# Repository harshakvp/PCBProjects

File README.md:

# PCB Design Projects

A collection of PCB design projects developed as part of my learning journey in electronics, embedded systems, and hardware design. This repository contains projects created using industry-standard EDA tools such as **Altium Designer** and **KiCad**, along with design files, documentation, and manufacturing outputs.

---

## Projects

### 1. ESP32 With USB-C (Altium Designer)

A custom 4-layer ESP32-S3 development board featuring USB Type-C connectivity, USB-UART programming, onboard power regulation, and GPIO expansion headers.

**Project Directory:**  
[Altium/ESP32Design](https://github.com/harshakvp/PCBProjects/tree/main/Altium/ESP32Design)

---

### 2. Quadratic Boost Converter PCB Redesign (Altium Designer)

A 2-layer PCB redesign of the published IEEE Quadratic Boost Converter featuring a high-gain non-isolated DC-DC converter topology, external PWM input interface, TC4420 MOSFET gate driver, IRF3710 power MOSFET, and manufacturing-ready design outputs.

**Project Directory:**  
[Altium/QuadraticConverter](https://github.com/harshakvp/PCBProjects/tree/main/Altium/QuadraticConverter)

---

### 3. Four Quadrant DC Motor Drive (Altium Designer)

A custom 2-layer 12V four quadrant DC motor drive featuring forward motoring, reverse motoring, and dynamic braking in both forward and reverse directions.

**Project Directory:**  
[Altium/FourQuadrantDCMotorDrive](https://github.com/harshakvp/PCBProjects/tree/main/Altium/FourQuadrantDCMotorDrive)

---

### 4. IR Proximity Sensor (KiCad)

A compact IR-based proximity sensing circuit designed using KiCad.

**Project Directory:**  
[KiCad/IR-Proximity-Sensor](https://github.com/harshakvp/PCBProjects/tree/main/KiCAD/IR%20Proximity%20Sensor)

---

## Repository Structure

```text
PCBProjects/
│
├── Altium/
│   ├── ESP32Design/
│   ├── QuadraticConverter/
│   └── FourQuadrantDCMotorDrive/
│
├── KiCad/
│   └── IR-Proximity-Sensor/
│
└── README.md
```

---

## Tools Used

- Altium Designer
- KiCad
- Git
- GitHub

---

## Author

### Harshak V P

Electrical and Electronics Engineering Undergraduate  
Vellore Institute of Technology (VIT), Vellore

#### Connect

- GitHub: [harshakvp](https://github.com/harshakvp)
- LinkedIn: [Harshak V P](https://www.linkedin.com/in/harshakvp/)
- Portfolio: [harshakvp.dev](https://chain-science-5eb.notion.site/HARSHAK-V-P-4f4889ae8ebf4c05a5790637c39213ba)
- Email: [harshakvp.contact@gmail.com](mailto:harshakvp.contact@gmail.com)

---

This repository is maintained for learning, experimentation, and open-source hardware development. Feel free to explore, use, modify, and build upon these projects.

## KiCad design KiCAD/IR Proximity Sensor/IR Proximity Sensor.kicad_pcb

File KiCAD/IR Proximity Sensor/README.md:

# IR Proximity Sensor

A compact IR-based proximity sensor designed using **KiCad**. This project demonstrates schematic design, PCB layout, routing, and 3D PCB visualization workflows.

---

## PCB Design

### Schematic

### PCB Layout

### 3D Model

---

## Repository Structure

```text
IR Proximity Sensor/
│
├── IR Proximity Sensor.kicad_sch
├── IR Proximity Sensor.kicad_pcb
├── IR Proximity Sensor.kicad_pro
├── IR Proximity Sensor.kicad_prl
└── README.md
```

---

## Getting Started

### Clone Repository

```bash
git clone https://github.com/harshakvp/PCBProjects.git
```

### Navigate to Project

```bash
cd PCBProjects/KiCAD/IR\ Proximity\ Sensor
```

### Open in KiCad

```text
IR Proximity Sensor.kicad_pro
```

---

## Tools Used

* KiCad
* Git
* GitHub

---

## Author

### Harshak V P

Electrical and Electronics Engineering Undergraduate
Vellore Institute of Technology (VIT), Vellore

#### Connect

* GitHub: [harshakvp](https://github.com/harshakvp)
* LinkedIn: [Harshak V P](https://www.linkedin.com/in/harshakvp/)
* Portfolio: [harshakvp.dev](https://chain-science-5eb.notion.site/HARSHAK-V-P-4f4889ae8ebf4c05a5790637c39213ba)
* Email: [harshakvp.contact@gmail.com](mailto:harshakvp.contact@gmail.com)

Feel free to open an issue, submit improvements, or reach out regarding the project.

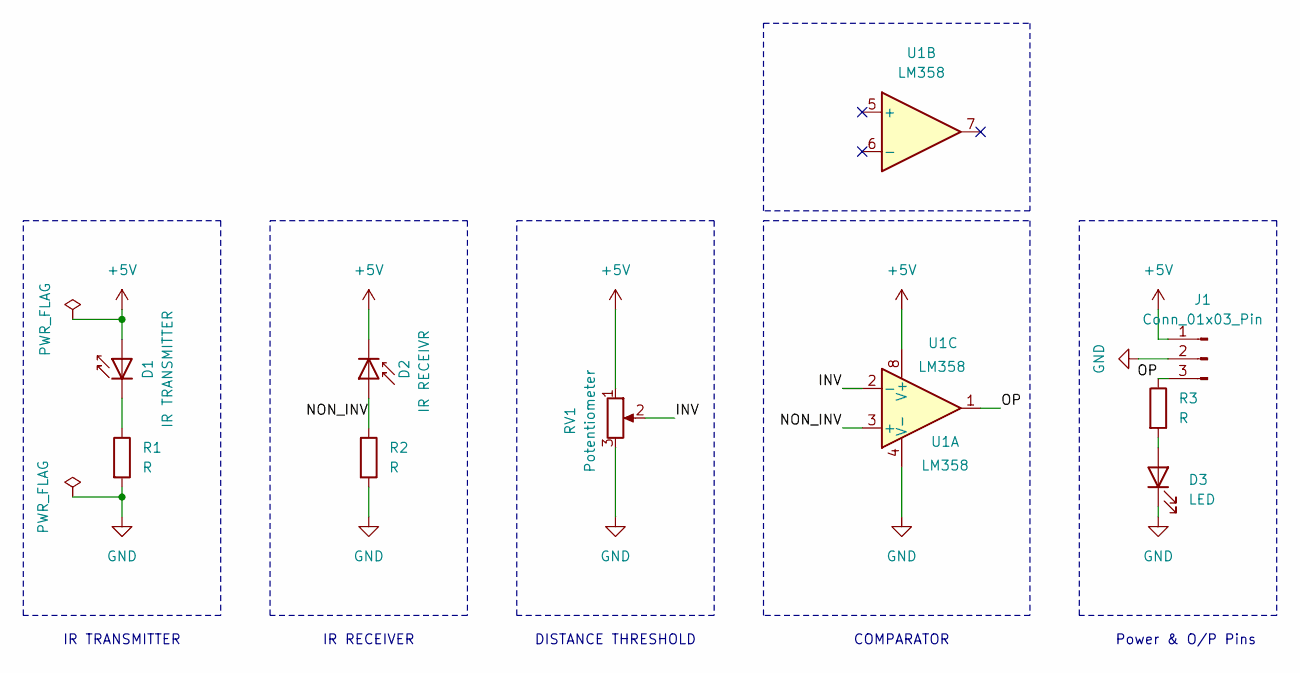
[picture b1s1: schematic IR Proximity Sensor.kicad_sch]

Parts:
D1: IR TRANSMITTER; LED_D3.0mm_Horizontal_O3.81mm_Z2.0mm
D2: IR RECEIVR; LED_D3.0mm_Horizontal_O3.81mm_Z2.0mm
D3: LED; LED_1206_3216Metric
J1: Conn_01x03_Pin; PinHeader_1x03_P2.54mm_Horizontal
R1, R2, R3: R; R_1206_3216Metric
RV1: Potentiometer; TRIM_3362P-1-103
U1: LM358; TSSOP-8_3x3mm_P0.65mm

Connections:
+5V: D1.2 (A), D2.1 (K), J1.1, RV1.1, U1.8 (V+)
/INV: RV1.2, U1.2 (-)
/NON_INV: D2.2 (A), R2.1, U1.3 (+)
/OP: J1.3, R3.1, U1.1
GND: D3.1 (K), J1.2, R1.2, R2.2, RV1.3, U1.4 (V-)
unnamed: D1.1 (K), R1.1
unnamed: D3.2 (A), R3.2

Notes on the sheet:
DISTANCE THRESHOLD
COMPARATOR
IR TRANSMITTER
IR RECEIVER
Power & O/P Pins

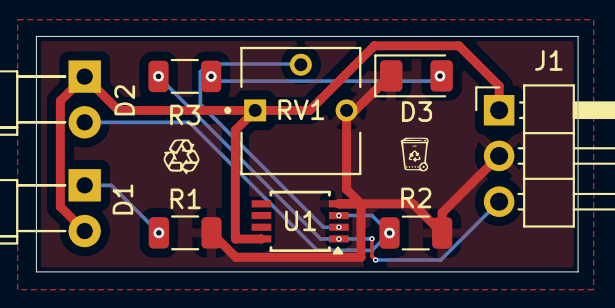
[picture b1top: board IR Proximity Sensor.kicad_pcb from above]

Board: 2 copper layers, 30.1 x 13.1 mm, 9 parts (0 on the bottom side), 7 nets.

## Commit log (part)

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2026-01-02 Local files updated
2026-01-04 Created ESP32 Symbol
2026-01-06 Created capacitor symbols for the schematic
2026-01-07 Added net labels
2026-01-07 New changes made
2026-01-07 Made changes in the schematic library
2026-01-09 Created schematics for reset and reboot button
2026-03-29 Created symbol for USB-C connector
2026-03-31 Updated USB-C connector 1 schematics
2026-05-22 Schematics: Protection Diodes & Power Jumpers
2026-05-24 Schematid: USB To UART
2026-05-24 Schematics: Updated USB To UART and Created Serial Signal Handling Circuit
2026-05-26 Schematics: GPIO Headers
2026-05-27 Schematics: First revision completed, and electrical rule check completed
2026-05-28 Schematic: Updated footprint for - regulator, USB to UART, resistor, transistor, push button
2026-05-30 Schematic: Added footprint for capacitors and connecting headers
2026-05-31 Schematic: Added footprint for all the components - electrical rule check with no errors
2026-06-01 PCB Layout: Placed USB C ports, headers, push buttons, USB to UART converter, ESP32, regulator on the PCB layout
2026-06-02 PCB Layout: Placed protection diodes, resistors and capacitors of USB connector 1 and 2 and USB to UART converter
2026-06-02 PCB Layout: Updated
2026-06-05 PCB Layout: Update v1.0
2026-06-05 PCB Layout: Update v1.1
2026-06-06 PCB Layout: Update v1.2
2026-06-07 PCB Layout: Applied differential pair length matching
2026-06-09 PCB Layout: Design rule check v1.0 - 553 errors
2026-06-09 PCB Layout: Added polygon pours around power pins and ground pins
2026-06-09 Commit test
2026-06-11 PCB Layout: Placed component desiginators, Design rule check v1.1 - 3 errors (Because of 3 not fitted resistors)
2026-06-11 Generated gerber files, NC drill files, assembly files, pick and place file - Project completed
2026-06-12 Added ready to use production files
2026-06-12 Added schematic and PCB layout snapshots
2026-06-13 FQDMD: Initial project configuration
2026-06-15 Schematics: Completed IR2110 gate driver & MOSFET
2026-06-15 Schematic: Schematic revision 1 completed
2026-06-15 Schematic: Completed, Electrical rule check with 0 errors
2026-06-16 Schematic: Assigned footprint and 3D model for the gate driver - IR2110
2026-06-17 Footprint & 3D model assignment work
2026-06-19 PCB Layout: Initial component placement
2026-06-20 PCB Layout: Drawn ploygon pours for power nets and high current nets
2026-06-21 PCB Layout: Ran DRC, rectifying design errors
2026-06-21 PCB Layout: Rectifyied all the DRC errors, prittyfied the board, minor corrections pending
2026-06-22 Project completed
2026-06-22 Added figures
